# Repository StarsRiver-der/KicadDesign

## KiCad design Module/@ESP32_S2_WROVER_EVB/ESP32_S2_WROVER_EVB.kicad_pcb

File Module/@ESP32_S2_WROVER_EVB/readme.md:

# ESP32-S2-WROVER 评估板 - SmartKnob
* 核心：ESP32-S2-WROVER 4N8R (4MB ROM,8M RAM)
* 串口：CP2102
* 电源：3.3V(MP2145),9V或可调(MP3431)
* 传感：光传感器VEML7700、温度传感器TMP117、6轴加速度传感器BMI160、磁编码器MT6701
* 外设：240x240 LCD串口屏幕(GC9401)、电容触摸屏(CST816)、SD卡、SK6812可编程LED、6PWM驱动器(TMC3600)、ADC(ADS122C04)
* 电机：BLDC-GM4018H

# 功能
* 智能旋钮，参考链接：https://www.youtube.com/watch?v=ip641WmY4pA

# 说明
### 工作模式介绍
* 旋转Knob，改变参数 (通过磁编码器检测)
* 按压Knob，模式切换 (通过SW1微动开关检测)
* Knob根据远程指令\传感器参数自动旋转 (通过控制电机转动)
### 器件功能
* VEML7700 提供环境光强度检测
* TMP117 提供室内温度检测
* BMI160 提供本设备姿态检测
* MT6701 检测电机精确旋转角度
* TMC3600 驱动BLDC电机，提供旋转反馈
* ADS122C04 24位低速高精度ADC，外接模拟信号传感器，如气体传感器、应变片
### 器件控制方式
* VEML7700、TMP117、BMI160、MT6701、ADS122C04、电容屏通过一个I2C总线控制
* LCD串口屏幕、SD卡通过一个SPI串口控制，其中LDC为非标准的四线SPI（CS、SLC、DC、SDA）
* GM4018H通过6线PWM控制

# 预览

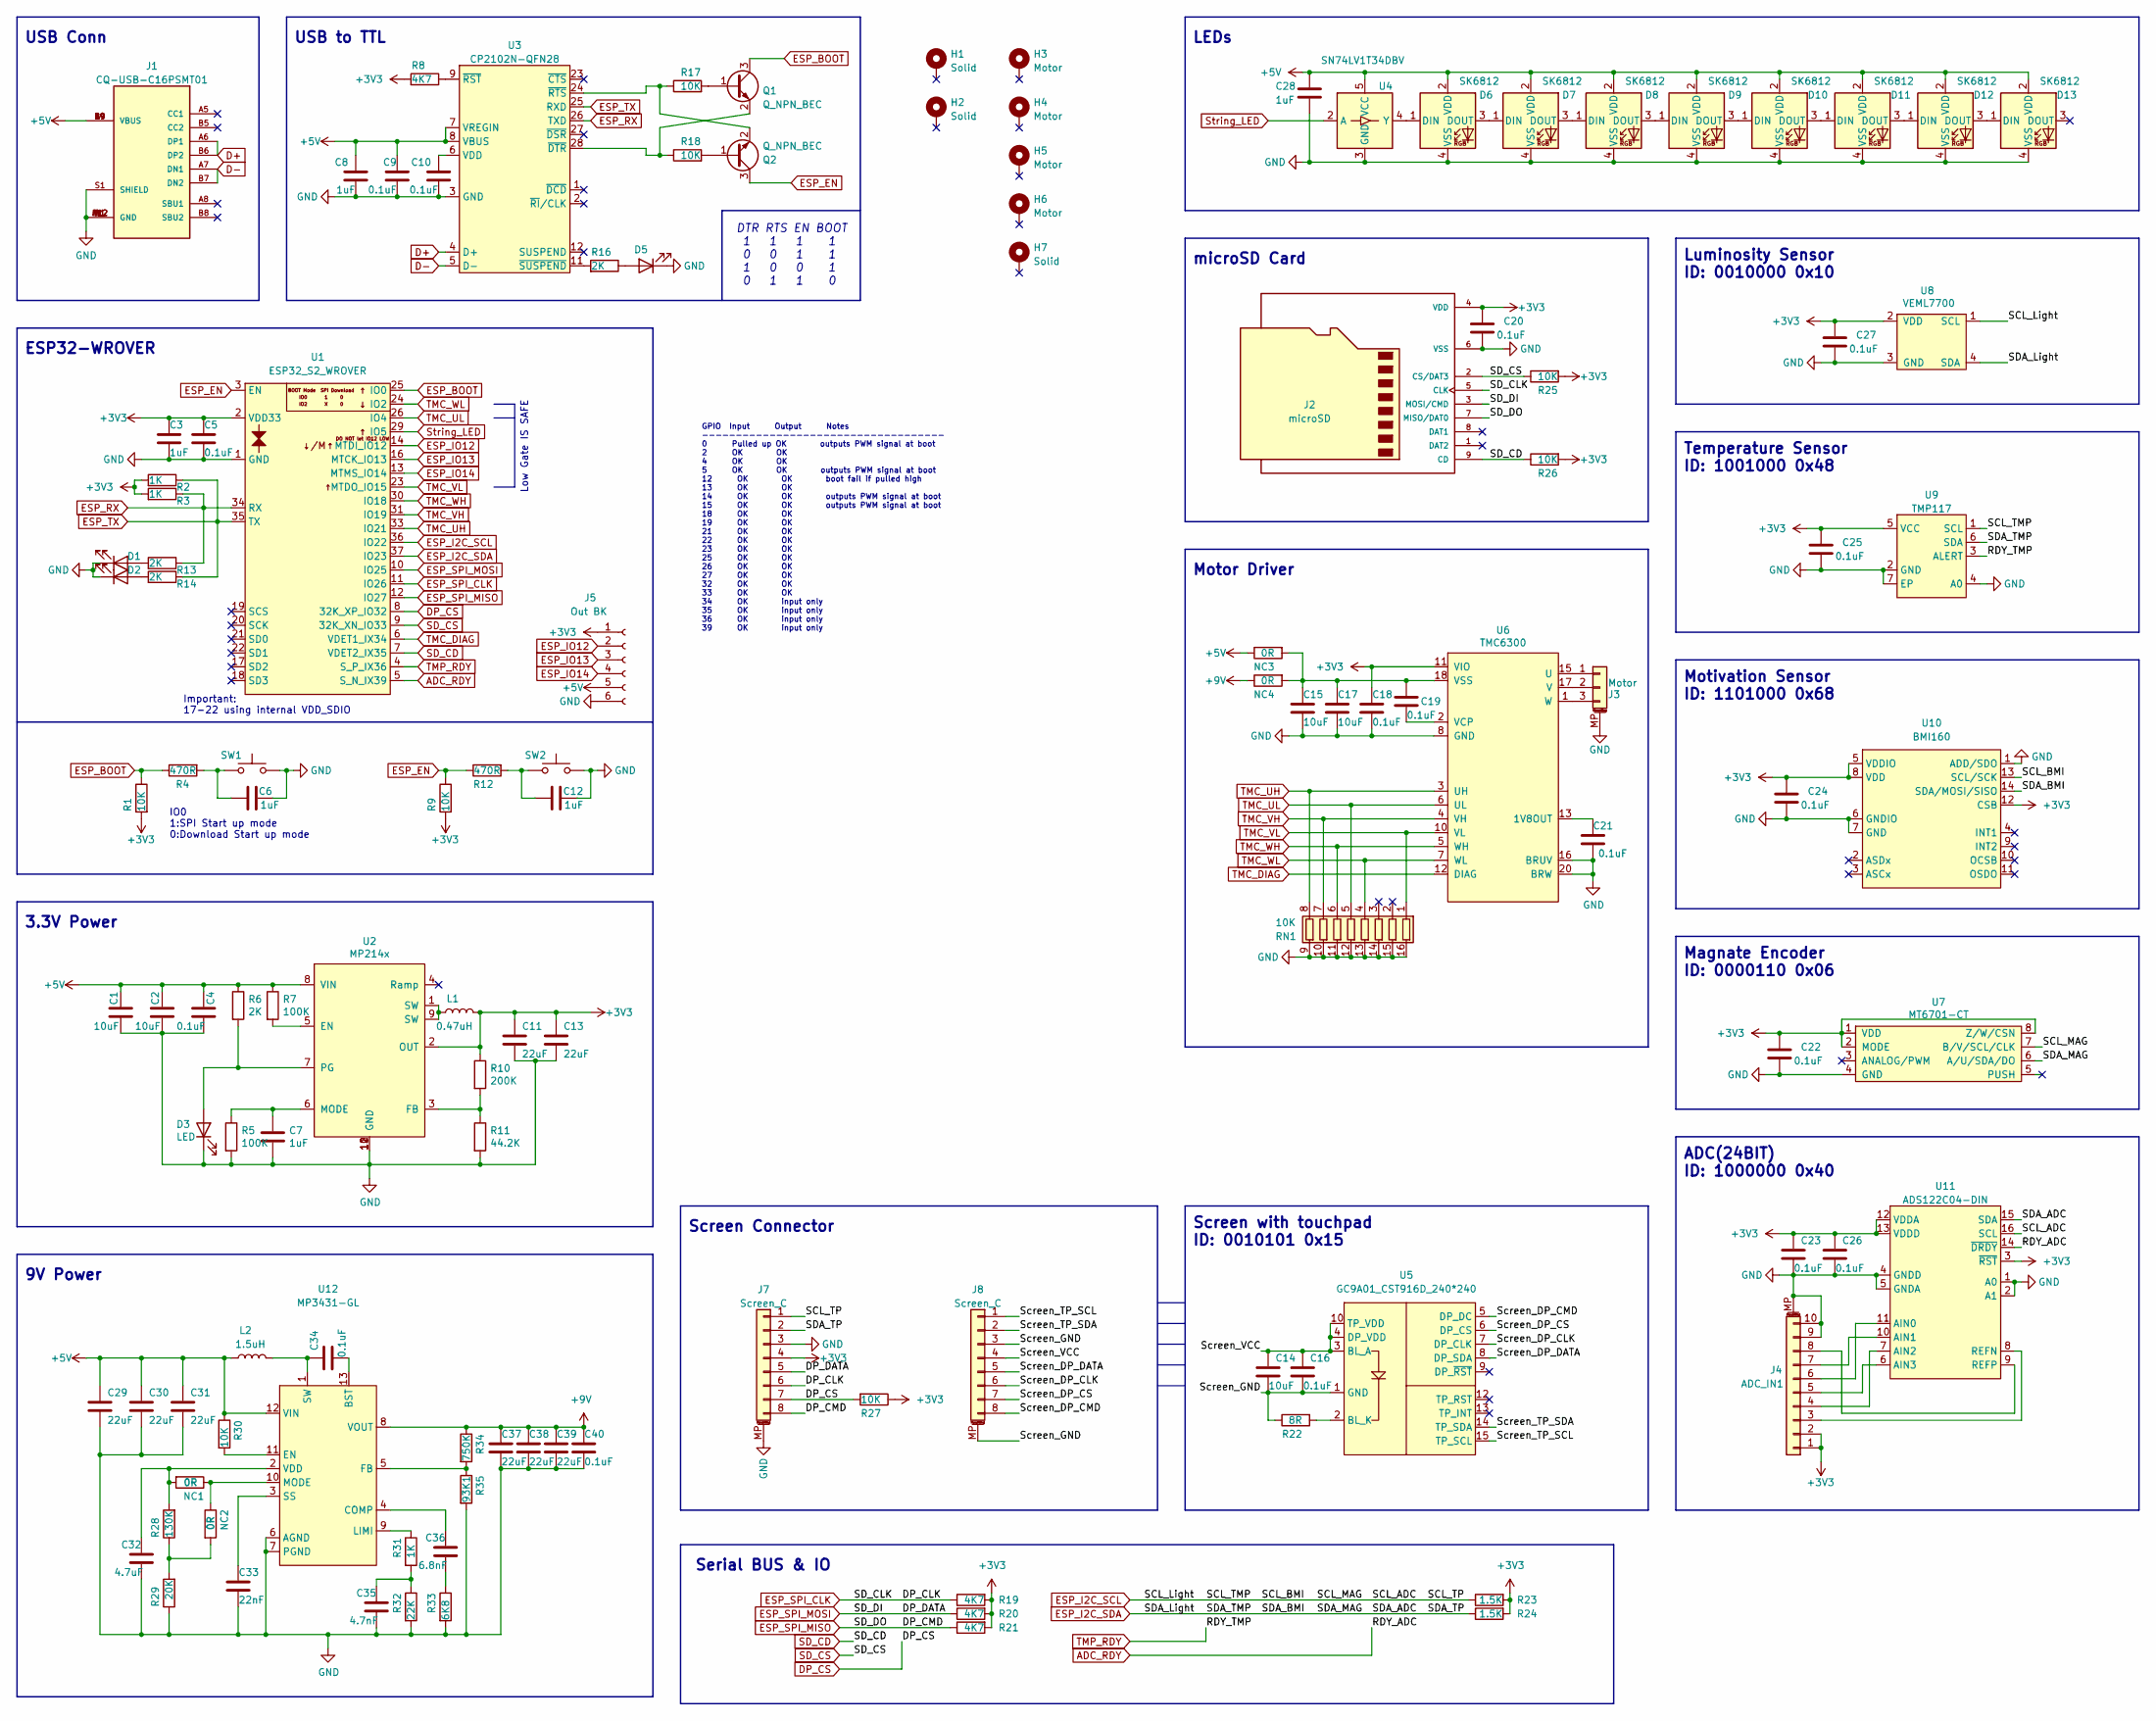
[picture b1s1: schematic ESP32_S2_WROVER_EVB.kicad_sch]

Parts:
C1, C2, C15, C17: 10uF; C_0603_1608Metric
C3, C6, C7, C8, C12, C28: 1uF; C_0402_1005Metric
C4, C5, C9, C10, C16, C18, C19, C20, C21, C22, C23, C24, C25, C26, C27, C34, C40: 0.1uF; C_0402_1005Metric
C11, C13, C29, C30, C31, C37, C38, C39: 22uF; C_0603_1608Metric
C14: 10uF; C_0402_1005Metric
C32: 4.7uF; C_0402_1005Metric
C33: 22nF; C_0402_1005Metric
C35: 4.7nF; C_0402_1005Metric
C36: 6.8nF; C_0402_1005Metric
D1, D2, D3, D5: LED; LED_0402_1005Metric
D6, D7, D8, D9, D10, D11, D12, D13: SK6812; SK6812-4020
H1, H2: Solid; MountingHole_2.2mm_M2_Pad_Via
H3, H4, H5, H6: Motor; MountingHole_3.2mm_M3_Pad_Via
H7: Solid; MountingHole_3.2mm_M3_Pad_Via
J1: CQ-USB-C16PSMT01; USB_C_Receptacle_XKB_U262-16XN-4BVC11; PARTREV A
J2: microSD; PARTREV A
J3: Motor; JST_PH_S3B-PH-SM4-TB_1x03-1MP_P2.00mm_Horizontal; LCSC C293630
J4: ADC_IN1; TE_1-84953-0_1x10-1MP_P1.0mm_Horizontal
J5: Out BK; PinHeader_1x06_P2.54mm_Vertical
J7, J8: Screen_C; TE_84953-8_1x08-1MP_P1.0mm_Horizontal
L1: 0.47uH; L_Taiyo-Yuden_NR-40xx
L2: 1.5uH; L_Wuerth_HCI-5040
NC1, NC2: 0R; R_0402_1005Metric
NC3, NC4: 0R; R_0805_2012Metric
Q1, Q2: Q_NPN_BEC; SOT-23
R1, R9, R17, R18, R25, R26, R27, R30: 10K; R_0402_1005Metric
R2, R3, R31: 1K; R_0402_1005Metric
R4, R12: 470R; R_0402_1005Metric
R5, R7: 100K; R_0402_1005Metric
R6, R13, R14, R16: 2K; R_0402_1005Metric
R8, R19, R20, R21: 4K7; R_0402_1005Metric
R10: 200K; R_0402_1005Metric
R11: 44.2K; R_0402_1005Metric
R22: 8R; R_0603_1608Metric
R23, R24: 1.5K; R_0402_1005Metric
R28: 130K; R_0402_1005Metric
R29: 20K; R_0402_1005Metric
R32: 22K; R_0402_1005Metric
R33: 6K8; R_0402_1005Metric
R34: 750K; R_0402_1005Metric
R35: 93K1; R_0402_1005Metric
RN1: 10K; R_Array_Convex_8x0602
SW1: SW_Push; SW_SPST_EVQP0
SW2: SW_Push; SW_Push_1P1T_NO_Vertical_Wuerth_434133025816
U1: ESP32_S2_WROVER; ESP32-S2-WROVER
U2: MP214x; MP2145
U3: CP2102N-QFN28; QFN-28-1EP_5x5mm_P0.5mm_EP3.35x3.35mm
U4: SN74LV1T34DBV; SOT-23-5
U5: GC9A01_CST916D_240*240; TE_1-1734839-5_1x15-1MP_P0.5mm_Horizontal
U6: TMC6300; QFN-20-1EP_3x3mm_P0.4mm_EP1.65x1.65mm; Digikey TMC6300-LA-T
U7: MT6701-CT; SOIC-8_3.9x4.9mm_P1.27mm; LCSC C2856764
U8: VEML7700; Digikey VEML7700-TT
U9: TMP117; WSON-6-1EP_2x2mm_P0.65mm_EP1x1.6mm
U10: BMI160; Bosch_LGA-14_3x2.5mm_P0.5mm
U11: ADS122C04-DIN; TSSOP-16_4.4x5mm_P0.65mm
U12: MP3431-GL; MP3431

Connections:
+3V3: C3.1, C5.1, C11.1, C13.1, C18.1, C20.1, C22.1, C23.1, C24.1, C25.1, C26.1, C27.1, J2.4 (VDD), J4.1, J4.2, J5.1, J7.4, L1.2, R1.2, R2.2, R3.2, R8.2, R9.2, R10.1, R19.2, R20.2, R21.2, R23.2, R24.2, R25.2, R26.2, R27.1, U1.2 (VDD33), U2.2 (OUT), U6.11 (VIO), U7.1 (VDD), U7.2 (MODE), U7.8 (Z/W/CSN), U8.2 (VDD), U9.5 (VCC), U10.5 (VDDIO), U10.8 (VDD), U10.12 (CSB), U11.3 (~RST), U11.12 (VDDA), U11.13 (VDDD)
+5V: C1.1, C2.1, C4.1, C8.2, C9.2, C28.1, C29.1, C30.1, C31.1, D6.2 (VDD), D7.2 (VDD), D8.2 (VDD), D9.2 (VDD), D10.2 (VDD), D11.2 (VDD), D12.2 (VDD), D13.2 (VDD), J1.A4 (VBUS), J1.A9 (VBUS), J1.B4 (VBUS), J1.B9 (VBUS), J5.5, L2.1, NC3.1, R6.1, R7.1, R30.1, U2.8 (VIN), U3.7 (VREGIN), U3.8 (VBUS), U4.5 (VCC), U12.12 (VIN)
+9V: C37.1, C38.1, C39.1, C40.1, NC4.1, R34.1, U12.8 (VOUT)
/Screen_DP_CLK: J8.6, U5.7 (DP_CLK)
/Screen_DP_CMD: J8.8, U5.5 (DP_DC)
/Screen_DP_CS: J8.7, U5.6 (DP_CS)
/Screen_DP_DATA: J8.5, U5.8 (DP_SDA)
/Screen_GND: C14.2, C16.2, J8.3, J8.MP (MountPin), R22.1, U5.1 (GND), U5.11 (GND), U5.MP
/Screen_TP_SCL: J8.1, U5.15 (TP_SCL)
/Screen_TP_SDA: J8.2, U5.14 (TP_SDA)
/Screen_VCC: C14.1, C16.1, J8.4, U5.3 (BL_A), U5.4 (DP_VDD), U5.10 (TP_VDD)
ADC_RDY: U1.5 (S_N_IX39), U11.14 (~DRDY)
D+: J1.A6 (DP1), J1.B6 (DP2), U3.4 (D+)
D-: J1.A7 (DN1), J1.B7 (DN2), U3.5 (D-)
DP_CS: J7.7, R27.2, U1.8 (32K_XP_IO32)
ESP_BOOT: Q1.3 (C), R1.1, R4.1, U1.25 (IO0)
ESP_EN: Q2.3 (C), R9.1, R12.1, U1.3 (EN)
ESP_I2C_SCL: J7.1, R23.1, U1.36 (IO22), U7.7 (B/V/SCL/CLK), U8.1 (SCL), U9.1 (SCL), U10.13 (SCL/SCK), U11.16 (SCL)
ESP_I2C_SDA: J7.2, R24.1, U1.37 (IO23), U7.6 (A/U/SDA/DO), U8.4 (SDA), U9.6 (SDA), U10.14 (SDA/MOSI/SISO), U11.15 (SDA)
ESP_IO12: J5.2, U1.14 (MTDI_IO12)
ESP_IO13: J5.3, U1.16 (MTCK_IO13)
ESP_IO14: J5.4, U1.13 (MTMS_IO14)
ESP_RX: R3.1, R13.1, U1.34 (RX), U3.26 (TXD)
ESP_SPI_CLK: J2.5 (CLK), J7.6, R19.1, U1.11 (IO26)
ESP_SPI_MISO: J2.7 (MISO/DAT0), J7.8, R21.1, U1.12 (IO27)
ESP_SPI_MOSI: J2.3 (MOSI/CMD), J7.5, R20.1, U1.10 (IO25)
ESP_TX: R2.1, R14.1, U1.35 (TX), U3.25 (RXD)
GND: C1.2, C2.2, C3.2, C4.2, C5.2, C6.2, C7.2, C8.1, C9.1, C10.2, C11.2, C12.2, C13.2, C15.2, C17.2, C18.2, C20.2, C21.1, C22.2, C23.2, C24.2, C25.2, C26.2, C27.2, C28.2, C29.2, C30.2, C31.2, C32.2, C33.2, C35.2, C37.2, C38.2, C39.2, C40.2, D1.1 (K), D2.1 (K), D3.1 (K), D5.1 (K), D6.4 (VSS), D7.4 (VSS), D8.4 (VSS), D9.4 (VSS), D10.4 (VSS), D11.4 (VSS), D12.4 (VSS), D13.4 (VSS), J1.A1 (GND), J1.A12 (GND), J1.B1 (GND), J1.B12 (GND), J1.S1 (SHIELD), J2.6 (VSS), J2.10 (SHIELD), J3.MP (MountPin), J4.9, J4.10, J4.MP (MountPin), J5.6, J7.3, J7.MP (MountPin), R5.2, R11.2, R29.1, R32.2, R33.2, R35.2, RN1.9 (R8.2), RN1.10 (R7.2), RN1.11 (R6.2), RN1.12 (R5.2), RN1.13 (R4.2), RN1.14 (R3.2), RN1.15 (R2.2), RN1.16 (R1.2), SW1.2, SW2.2, U1.1 (GND), U1.15 (GND), U1.38 (GND), U1.39 (GND), U2.10 (GND), U2.11 (GND), U2.12 (GND), U3.3 (GND), U3.29 (GND), U4.3 (GND), U6.8 (GND), U6.9 (GND), U6.14 (GND), U6.16 (BRUV), U6.20 (BRW), U6.21 (EP), U7.4 (GND), U8.3 (GND), U9.2 (GND), U9.4 (A0), U9.7 (EP), U10.1 (ADD/SDO), U10.6 (GNDIO), U10.7 (GND), U11.1 (A0), U11.2 (A1), U11.4 (GNDD), U11.5 (GNDA), U12.6 (AGND), U12.7 (PGND)
unnamed: C6.1, R4.2, SW1.1
unnamed: C7.1, R5.1, U2.6 (MODE)
unnamed: C10.1, U3.6 (VDD)
unnamed: C12.1, R12.2, SW2.1
unnamed: C15.1, C17.1, C19.1, NC3.2, NC4.2, U6.18 (VSS)
unnamed: C19.2, U6.2 (VCP)
unnamed: C21.2, U6.13 (1V8OUT)
unnamed: C32.1, NC1.2, R28.2, U12.2 (VDD)
unnamed: C33.1, U12.3 (SS)
unnamed: C34.1, L2.2, U12.1 (SW)
unnamed: C34.2, U12.13 (BST)
unnamed: C35.1, R31.2, R32.1
unnamed: C36.1, U12.4 (COMP)
unnamed: C36.2, R33.1
unnamed: D1.2 (A), R13.2
unnamed: D2.2 (A), R14.2
unnamed: D3.2 (A), R6.2, U2.7 (PG)
unnamed: D5.2 (A), R16.1
unnamed: D6.1 (DIN), U4.4 (Y)
unnamed: D6.3 (DOUT), D7.1 (DIN)
unnamed: D7.3 (DOUT), D8.1 (DIN)
unnamed: D8.3 (DOUT), D9.1 (DIN)
unnamed: D9.3 (DOUT), D10.1 (DIN)
unnamed: D10.3 (DOUT), D11.1 (DIN)
unnamed: D11.3 (DOUT), D12.1 (DIN)
unnamed: D12.3 (DOUT), D13.1 (DIN)
unnamed: J3.1, U6.15 (U)
unnamed: J3.2, U6.17 (V)
unnamed: J3.3, U6.1 (W)
unnamed: J4.3, U11.8 (REFN)
unnamed: J4.4, U11.7 (AIN2)
unnamed: J4.5, U11.6 (AIN3)
unnamed: J4.6, U11.11 (AIN0)
unnamed: J4.7, U11.10 (AIN1)
unnamed: J4.8, U11.9 (REFP)
unnamed: L1.1, U2.1 (SW), U2.9 (SW)
unnamed: NC1.1, NC2.1, U12.10 (MODE)
unnamed: NC2.2, R28.1, R29.2
unnamed: Q1.1 (B), R17.2
unnamed: Q1.2 (E), R18.1, U3.28 (~DTR)
unnamed: Q2.1 (B), R18.2
unnamed: Q2.2 (E), R17.1, U3.24 (~RTS)
unnamed: R7.2, U2.5 (EN)
unnamed: R8.1, U3.9 (~RST)
unnamed: R10.2, R11.1, U2.3 (FB)
unnamed: R16.2, U3.11 (~SUSPEND)
unnamed: R22.2, U5.2 (BL_K)
unnamed: R30.2, U12.11 (EN)
unnamed: R31.1, U12.9 (LIMI)
unnamed: R34.2, R35.1, U12.5 (FB)
SD_CD: J2.9 (CD), R26.1, U1.7 (VDET2_IX35)
SD_CS: J2.2 (CS/DAT3), R25.1, U1.9 (32K_XN_IO33)
String_LED: U1.29 (IO5), U4.2 (A)
TMC_DIAG: U1.6 (VDET1_IX34), U6.12 (DIAG)
TMC_UH: RN1.8 (R8.1), U1.33 (IO21), U6.3 (UH)
TMC_UL: RN1.5 (R5.1), U1.26 (IO4), U6.6 (UL)
TMC_VH: RN1.7 (R7.1), U1.31 (IO19), U6.4 (VH)
TMC_VL: RN1.1 (R1.1), U1.23 (MTDO_IO15), U6.10 (VL)
TMC_WH: RN1.6 (R6.1), U1.30 (IO18), U6.5 (WH)
TMC_WL: RN1.4 (R4.1), U1.24 (IO2), U6.7 (WL)
TMP_RDY: U1.4 (S_P_IX36), U9.3 (ALERT)

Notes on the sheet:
Magnate Encoder ID: 0000110 0x06
Screen with touchpad ID: 0010101 0x15
microSD Card
GPIO Input Output Notes ------------------------------------ 0 Pulled up OK outputs PWM signal at boot 2 OK OK 4 OK OK 5 OK OK outputs PWM signal at boot 12 OK OK boot fail if pulled high 13 OK OK 14 OK OK outputs PWM signal at boot 15 OK OK outputs PWM signal at boot 18 OK OK 19 OK OK 21 OK OK 22 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
Motor Driver
3.3V Power
ESP32-WROVER
Serial BUS & IO
Temperature Sensor ID: 1001000 0x48
USB to TTL
9V Power
Luminosity Sensor ID: 0010000 0x10
Motivation Sensor ID: 1101000 0x68
IO0 1:SPI Start up mode 0:Download Start up mode
USB Conn
DTR RTS EN BOOT 1 1 1 1 0 0 1 1 1 0 0 1 0 1 1 0
LEDs
Important: 17-22 using internal VDD_SDIO
Screen Connector
ADC(24BIT) ID: 1000000 0x40
Low Gate IS SAFE

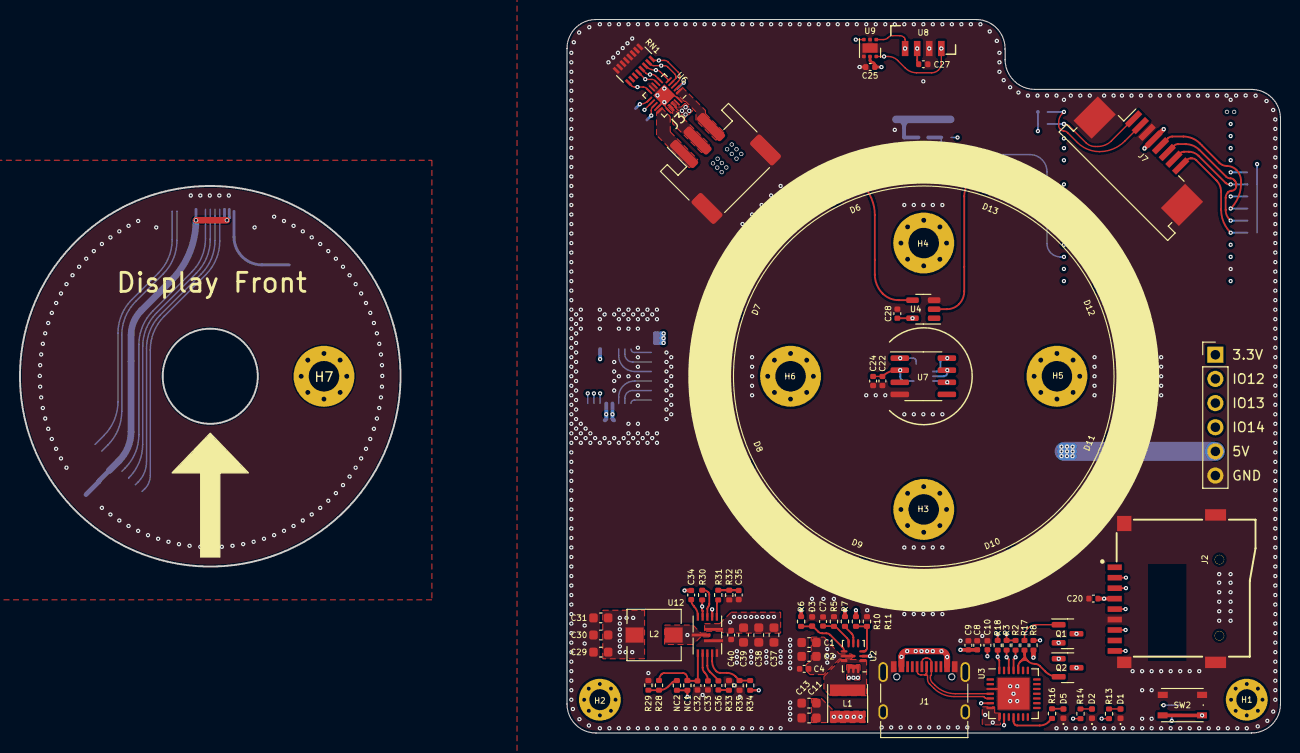
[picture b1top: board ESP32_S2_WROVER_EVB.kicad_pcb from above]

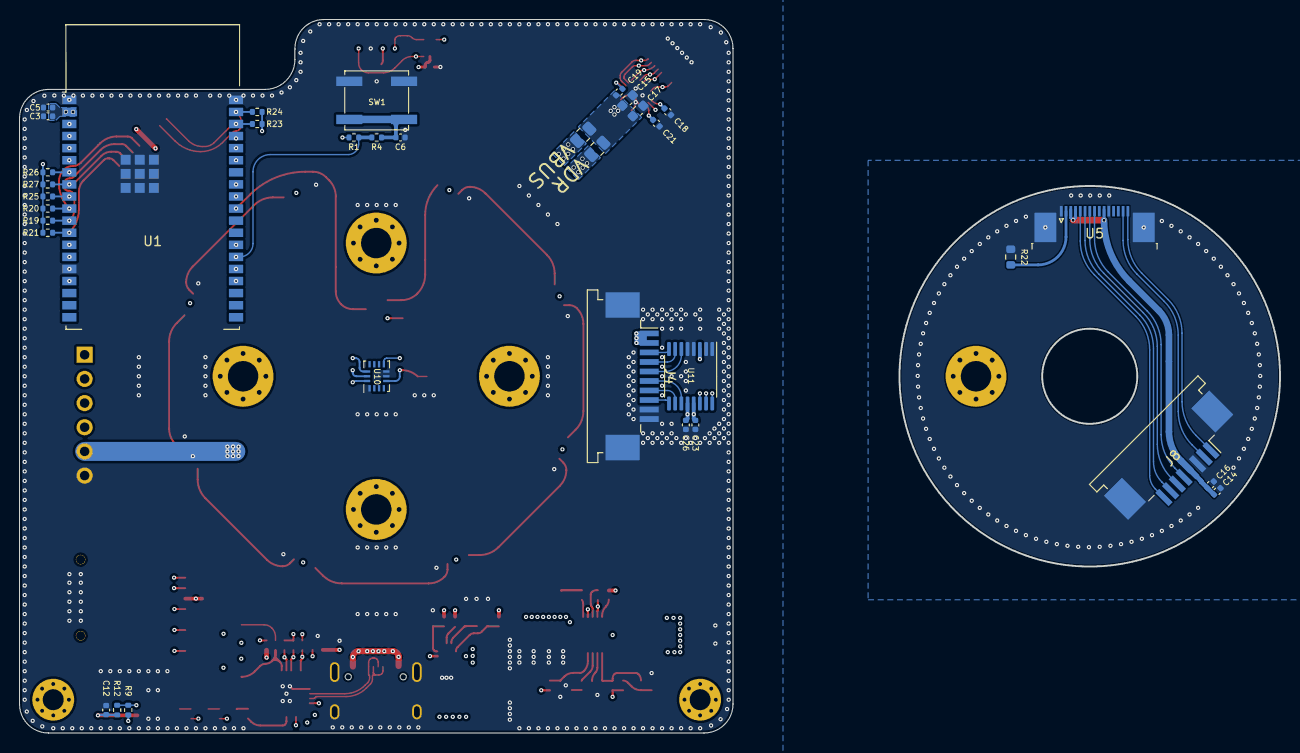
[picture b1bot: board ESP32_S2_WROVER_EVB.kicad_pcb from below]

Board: 4 copper layers, 75.0 x 75.0 mm, 123 parts (35 on the bottom side), 89 nets.

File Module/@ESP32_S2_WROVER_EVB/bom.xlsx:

元件 | 数量/板 | 值 | 封装 | 备注 | 数量 | 单价 | 总价
R00 | 2 | 0R | 0402 |  | 0 | 0
R000 | 2 | 0R | 0805 |  | 0 | 0
R1, R9, R17, R18, R25, R26, R27, R30 | 8 | 10K | 0402 |  | 0 | 0
R2, R3, R6, R16 | 4 | 2K | 0402 |  | 0 | 0
R4, R12 | 2 | 470R | 0402 |  | 0 | 0
R5, R7 | 2 | 100K | 0402 |  | 0 | 0
R8, R19, R20, R21 | 4 | 4K7 | 0402 |  | 0 | 0
R10 | 1 | 200K | 0402 |  | 0 | 0
R11 | 1 | 44.2K | 0402 |  | 0 | 0
R22 | 1 | 8R | 0603 |  | 0 | 0
R23, R24 | 2 | 1.5K | 0402 |  | 0 | 0
R28 | 1 | 130K | 0402 |  | 0 | 0
R29 | 1 | 20K | 0402 |  | 0 | 0
R31 | 1 | 1K | 0402 |  | 0 | 0
R32 | 1 | 22K | 0402 |  | 0 | 0
R33 | 1 | 6K8 | 0402 |  | 0 | 0
R34 | 1 | 750K | 0402 |  | 0 | 0
R35 | 1 | 93K1 | 0402 |  | 0 | 0
RN1 | 1 | 10K | 8x0602 | 排阻8x0602 | 0 | 0
L1 | 1 | 0.47uH | NR4020 | 磁胶电感 | 0 | 0
L2 | 1 | 1.5uH | 5040 |  | 0 | 0
C1, C2, C15, C17 | 4 | 10uF | 0603 |  | 0 | 0
C3, C6, C7, C8, C12, C28 | 6 | 1uF | 0402 |  | 0 | 0
C4, C5, C9, C10, C16, C18, C19, C20, C21, C22, C23, C24, C25, C26, C27, C34, C40 | 17 | 0.1uF | 0402 |  | 0 | 0
C11, C13, C29, C30, C31, C37, C38, C39 | 8 | 22uF | 0603 |  | 0 | 0
C14 | 1 | 10uF | 0402 |  | 0 | 0
C32 | 1 | 4.7uF | 0402 |  | 0 | 0
C33 | 1 | 22nF | 0402 |  | 0 | 0
C35 | 1 | 4.7nF | 0402 |  | 0 | 0
C36 | 1 | 6.8nF | 0402 |  | 0 | 0
D1, D2, D3, D5 | 4 | LED | 0402 |  | 0 | 0
D6, D7, D8, D9, D10, D11, D12, D13 | 8 | SK6812-4020 | SK6812-4020 | 侧发光，不能用WS2812 | 0 | 0
J1 | 1 | Type-C 16pin | Type-C 16pin | https://detail.tmall.com/item.htm?id=617881556896&spm=a1z09.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 | 0 | 0
J2 | 1 | microSD | microSD槽 | https://detail.tmall.com/item.htm?id=615194188570&spm=a1z09.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 | 0 | 0
J3 | 1 | Motor | PH2.00 3P卧贴 | https://item.taobao.com/item.htm?spm=a1z2k.11010449.931864.2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 | 0 | 0
J4 | 1 | ADC_IN1 | 抽拉上接 10p-1mm | https://item.taobao.com/item.htm?spm=a230r.1.14.29.5d1b6f3bt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 | 0 | 0
J7, J8 | 2 | Screen_C | 抽拉上接 8p-1mm | https://item.taobao.com/item.htm?spm=a230r.1.14.29.5d1b6f3bt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 | 0 | 0
U5 | 1 | Screen_Conn | 抽拉上接 15p-0.5mm | https://item.taobao.com/item.htm?spm=a230r.1.14.29.5d1b6f3bt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 | 0 | 0
Q1, Q2 | 2 | S8050 - NPN | SOT-23 |  | 0 | 0
SW1 | 1 | SW_Push | 3.5mm | https://item.taobao.com/item.htm?spm=a230r.1.14.188.1c6d7fd0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 | 0 | 0
SW2 | 1 | SW_Push | 3*4*2.5 包脚 | https://detail.tmall.com/item.htm?id=654795333730&spm=a1z09.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 | 0 | 0
U1 | 1 | ESP32_S2_WROVER | ESP32-S2-WROVER |  | 0 | 0
U2 | 1 | MP2145 | MP2145 |  | 0 | 0
U3 | 1 | CP2102 | QFN28 |  | 0 | 0
U4 | 1 | SN74LV1T34DBV | SOT-23-5 |  | 0 | 0
U6 | 1 | TMC6300_LA | QFN-20 |  | 0 | 0
U7 | 1 | MT6701 | SOIC-8 |  | 0 | 0
U8 | 1 | VEML7700 | VEML7700 |  | 0 | 0
U9 | 1 | TMP117 | WSON-6 |  | 0 | 0
U10 | 1 | BMI160 | LGA-14 |  | 0 | 0
U11 | 1 | ADS122C04-DIN | TSSOP-16 |  | 0 | 0
U12 | 1 | MP3431-GL | MP3431 |  | 0 | 0
M1 | 1 | 电机 | GM4018H | https://item.taobao.com/item.htm?spm=a1z0d.6639537/tb.199719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 | 0 | 0

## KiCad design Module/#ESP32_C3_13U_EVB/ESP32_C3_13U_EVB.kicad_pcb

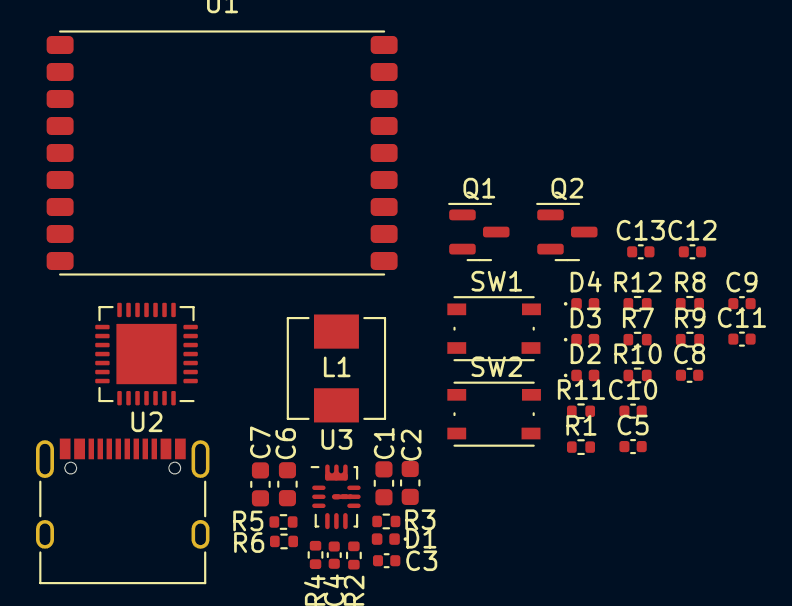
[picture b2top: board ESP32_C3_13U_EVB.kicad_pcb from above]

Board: 2 copper layers, 38 parts (0 on the bottom side), 22 nets, no tracks yet.

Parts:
C1, C2: 10uF; C_0603_1608Metric
C3, C8, C9, C11: 0.1uF; C_0402_1005Metric
C4, C5, C10, C12, C13: 1uF; C_0402_1005Metric
C6, C7: 22uF; C_0603_1608Metric
D1, D2, D3, D4: LED; LED_0402_1005Metric
J1: CQ-USB-C16PSMT01; USB_C_Receptacle_XKB_U262-16XN-4BVC11
L1: 0.47uH; L_Sunlord_MWSA0518_5.4x5.2mm
Q1, Q2: Q_NPN_BEC; SOT-23
R1: 4K7; R_0402_1005Metric
R2, R4: 100K; R_0402_1005Metric
R3, R7, R8, R9: 2K; R_0402_1005Metric
R5: 200K; R_0402_1005Metric
R6: 44.2K; R_0402_1005Metric
R10, R11, R12: 10K; R_0402_1005Metric
SW1, SW2: SW_Push; SW_Push_1P1T_NO_Vertical_Wuerth_434133025816
U1: C3_13U; ESP32_C3_13U
U2: CP2102N-QFN28; QFN-28-1EP_5x5mm_P0.5mm_EP3.35x3.35mm
U3: MP214x; MP2145

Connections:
3.3V: C6.1, C7.1, C10.1, C11.1, L1.2, R1.2, R5.1, R8.2, R9.2, R12.2, U1.1 (VCC), U3.2 (OUT)
5V: C1.1, C2.1, C3.1, C5.2, C8.2, J1.A4 (VBUS), J1.A9 (VBUS), J1.B4 (VBUS), J1.B9 (VBUS), R3.1, R4.1, U2.7 (VREGIN), U2.8 (VBUS), U3.8 (VIN)
D+: J1.A6 (DP1), J1.B6 (DP2), U2.4 (D+)
D-: J1.A7 (DN1), J1.B7 (DN2), U2.5 (D-)
ESP_BOOT: C13.2, Q1.3 (C), R12.1, SW2.1, U1.8 (IO9)
ESP_EN: C12.2, Q2.3 (C), SW1.1, U1.2 (EN)
ESP_RX: D4.2 (A), R9.1, U1.11 (RX), U2.26 (TXD)
ESP_TX: D3.2 (A), R8.1, U1.12 (TX), U2.25 (RXD)
GND: C1.2, C2.2, C3.2, C4.2, C5.1, C6.2, C7.2, C8.1, C9.2, C10.2, C11.2, C12.1, C13.1, D1.1 (K), D2.1 (K), D3.1 (K), D4.1 (K), J1.A1 (GND), J1.A12 (GND), J1.B1 (GND), J1.B12 (GND), J1.S1 (SHIELD), R2.2, R6.2, SW1.2, SW2.2, U1.9 (GND), U2.3 (GND), U2.29 (GND), U3.10 (GND), U3.11 (GND), U3.12 (GND)
unnamed: C4.1, R2.1, U3.6 (MODE)
unnamed: C9.1, U2.6 (VDD)
unnamed: D1.2 (A), R3.2, U3.7 (PG)
unnamed: D2.2 (A), R7.1
unnamed: L1.1, U3.1 (SW), U3.9 (SW)
unnamed: Q1.1 (B), R10.2
unnamed: Q1.2 (E), R11.1, U2.28 (~DTR)
unnamed: Q2.1 (B), R11.2
unnamed: Q2.2 (E), R10.1, U2.24 (~RTS)
unnamed: R1.1, U2.9 (~RST)
unnamed: R4.2, U3.5 (EN)
unnamed: R5.2, R6.1, U3.3 (FB)
unnamed: R7.2, U2.11 (~SUSPEND)

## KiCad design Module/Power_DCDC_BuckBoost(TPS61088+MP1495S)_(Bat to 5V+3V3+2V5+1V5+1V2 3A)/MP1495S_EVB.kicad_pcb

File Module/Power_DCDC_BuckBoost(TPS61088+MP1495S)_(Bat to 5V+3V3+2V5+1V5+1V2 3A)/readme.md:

# 2.8V-4.2V 锂电池输入的 DCDC 单极性多轨电源
* 工作温度：0-85℃
* 5V、3v3、2v5、1v5、1v2多轨输出
* 最高20W输出

# 注意事项
* 使用Kicad6绘制

# 原理
见说明手册

# 接口
* 电压输入和控制输入：FPC_Hirose_FH12-14S
* 电压输出和控制输出：PCI_1x

# 预览

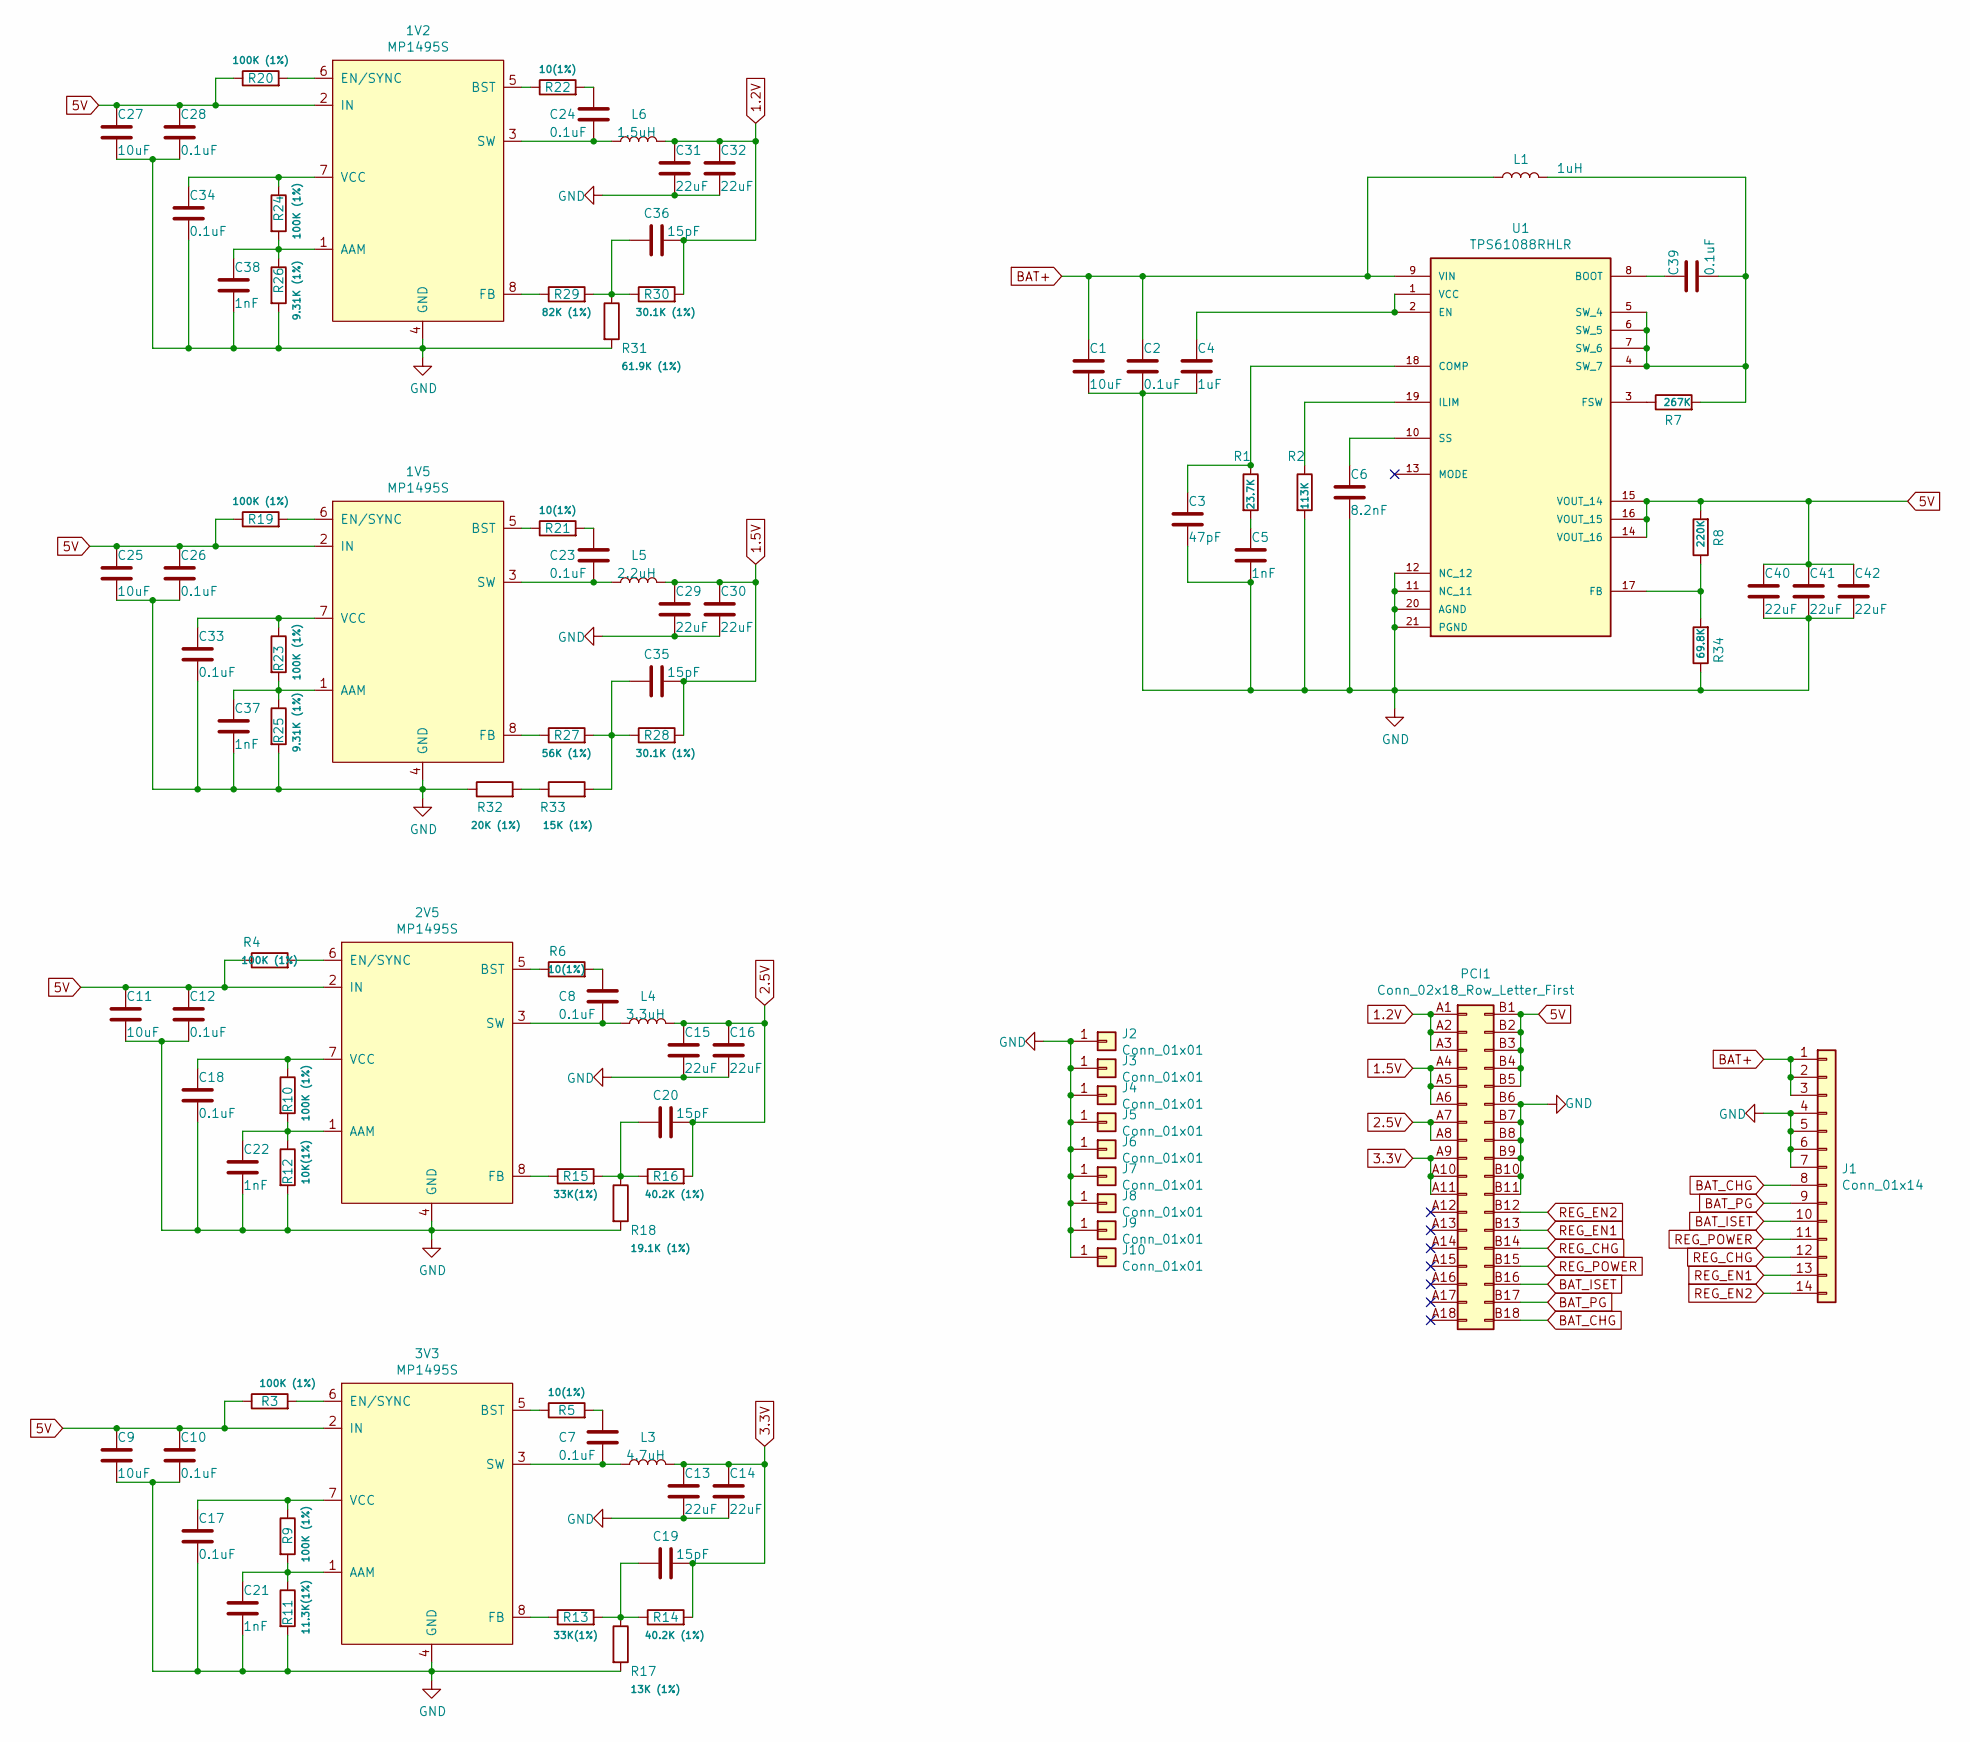
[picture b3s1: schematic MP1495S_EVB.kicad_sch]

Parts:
1V2, 1V5, 2V5, 3V3: MP1495S; SOT65P280X100-8N
C1, C9, C11, C25, C27: 10uF; C_0603_1608Metric
C2, C7, C8, C10, C12, C17, C18, C23, C24, C26, C28, C33, C34, C39: 0.1uF; C_0402_1005Metric
C3: 47pF; C_0402_1005Metric
C4: 1uF; C_0402_1005Metric
C5, C21, C22, C37, C38: 1nF; C_0402_1005Metric
C6: 8.2nF; C_0402_1005Metric
C13, C14, C15, C16, C29, C30, C31, C32, C40, C41, C42: 22uF; C_0603_1608Metric
C19, C20, C35, C36: 15pF; C_0402_1005Metric
J1: Conn_01x14; Hirose_FH12-14S-0.5SH_1x14-1MP_P0.50mm_Horizontal
J2, J3, J4, J5, J6, J7, J8, J9, J10: Conn_01x01; pad-6-1.5
L1: 1uH; L_Sunlord_MWSA0518_5.4x5.2mm
L3: 4.7uH; L_Sunlord_MWSA0518_5.4x5.2mm
L4: 3.3uH; L_Sunlord_MWSA0518_5.4x5.2mm
L5: 2.2uH; L_Sunlord_MWSA0518_5.4x5.2mm
L6: 1.5uH; L_Sunlord_MWSA0518_5.4x5.2mm
PCI1: Conn_02x18_Row_Letter_First; BUS_PCIexpress_x1
R1: 23.7K; R_0402_1005Metric
R2: 113K; R_0402_1005Metric
R3, R4, R9, R10, R19, R20, R23, R24: 100K (1%); R_0402_1005Metric
R5, R6, R21, R22: 10(1%); R_0402_1005Metric
R7: 267K; R_0402_1005Metric
R8: 220K; R_0402_1005Metric
R11: 11.3K(1%); R_0402_1005Metric
R12: 10K(1%); R_0402_1005Metric
R13, R15: 33K(1%); R_0402_1005Metric
R14, R16: 40.2K (1%); R_0402_1005Metric
R17: 13K (1%); R_0402_1005Metric
R18: 19.1K (1%); R_0402_1005Metric
R25, R26: 9.31K (1%); R_0402_1005Metric
R27: 56K (1%); R_0402_1005Metric
R28, R30: 30.1K (1%); R_0402_1005Metric
R29: 82K (1%); R_0402_1005Metric
R31: 61.9K (1%); R_0402_1005Metric
R32: 20K (1%); R_0402_1005Metric
R33: 15K (1%); R_0402_1005Metric
R34: 69.8K; R_0402_1005Metric
U1: TPS61088RHLR; IC_TPS61088RHLR; PARTREV 4219071/A 05/2017

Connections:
1.2V: C31.1, C32.1, C36.2, L6.2, PCI1.A1, PCI1.A2, PCI1.A3, R30.2
1.5V: C29.1, C30.1, C35.2, L5.2, PCI1.A4, PCI1.A5, PCI1.A6, R28.2
2.5V: C15.1, C16.1, C20.2, L4.2, PCI1.A7, PCI1.A8, R16.2
3.3V: C13.1, C14.1, C19.2, L3.2, PCI1.A9, PCI1.A10, PCI1.A11, R14.2
5V: 1V2.2 (IN), 1V5.2 (IN), 2V5.2 (IN), 3V3.2 (IN), C9.1, C10.1, C11.1, C12.1, C25.1, C26.1, C27.1, C28.1, C40.1, C41.1, C42.1, PCI1.B1, PCI1.B2, PCI1.B3, PCI1.B4, PCI1.B5, R3.1, R4.1, R8.2, R19.1, R20.1, U1.14 (VOUT_16), U1.15 (VOUT_14), U1.16 (VOUT_15)
BAT+: C1.1, C2.1, J1.1, J1.2, J1.3, L1.1, U1.9 (VIN)
BAT_CHG: J1.8, PCI1.B18
BAT_ISET: J1.10, PCI1.B16
BAT_PG: J1.9, PCI1.B17
GND: 1V2.4 (GND), 1V5.4 (GND), 2V5.4 (GND), 3V3.4 (GND), C1.2, C2.2, C3.2, C4.2, C5.2, C6.2, C9.2, C10.2, C11.2, C12.2, C13.2, C14.2, C15.2, C16.2, C17.2, C18.2, C21.2, C22.2, C25.2, C26.2, C27.2, C28.2, C29.2, C30.2, C31.2, C32.2, C33.2, C34.2, C37.2, C38.2, C40.2, C41.2, C42.2, J1.4, J1.5, J1.6, J1.7, J2.1, J3.1, J4.1, J5.1, J6.1, J7.1, J8.1, J9.1, J10.1, PCI1.B6, PCI1.B7, PCI1.B8, PCI1.B9, PCI1.B10, PCI1.B11, R2.2, R11.2, R12.2, R17.2, R18.2, R25.2, R26.2, R31.2, R32.1, R34.1, U1.11 (NC_11), U1.12 (NC_12), U1.20 (AGND), U1.21 (PGND)
unnamed: 1V2.1 (AAM), C38.1, R24.2, R26.1
unnamed: 1V2.3 (SW), C24.2, L6.1
unnamed: 1V2.5 (BST), R22.1
unnamed: 1V2.6 (EN/SYNC), R20.2
unnamed: 1V2.7 (VCC), C34.1, R24.1
unnamed: 1V2.8 (FB), R29.1
unnamed: 1V5.1 (AAM), C37.1, R23.2, R25.1
unnamed: 1V5.3 (SW), C23.2, L5.1
unnamed: 1V5.5 (BST), R21.1
unnamed: 1V5.6 (EN/SYNC), R19.2
unnamed: 1V5.7 (VCC), C33.1, R23.1
unnamed: 1V5.8 (FB), R27.1
unnamed: 2V5.1 (AAM), C22.1, R10.2, R12.1
unnamed: 2V5.3 (SW), C8.2, L4.1
unnamed: 2V5.5 (BST), R6.1
unnamed: 2V5.6 (EN/SYNC), R4.2
unnamed: 2V5.7 (VCC), C18.1, R10.1
unnamed: 2V5.8 (FB), R15.1
unnamed: 3V3.1 (AAM), C21.1, R9.2, R11.1
unnamed: 3V3.3 (SW), C7.2, L3.1
unnamed: 3V3.5 (BST), R5.1
unnamed: 3V3.6 (EN/SYNC), R3.2
unnamed: 3V3.7 (VCC), C17.1, R9.1
unnamed: 3V3.8 (FB), R13.1
unnamed: C3.1, R1.1, U1.18 (COMP)
unnamed: C4.1, U1.1 (VCC), U1.2 (EN)
unnamed: C5.1, R1.2
unnamed: C6.1, U1.10 (SS)
unnamed: C7.1, R5.2
unnamed: C8.1, R6.2
unnamed: C19.1, R13.2, R14.1, R17.1
unnamed: C20.1, R15.2, R16.1, R18.1
unnamed: C23.1, R21.2
unnamed: C24.1, R22.2
unnamed: C35.1, R27.2, R28.1, R33.2
unnamed: C36.1, R29.2, R30.1, R31.1
unnamed: C39.1, U1.8 (BOOT)
unnamed: C39.2, L1.2, R7.2, U1.4 (SW_7), U1.5 (SW_4), U1.6 (SW_5), U1.7 (SW_6)
unnamed: R2.1, U1.19 (ILIM)
unnamed: R7.1, U1.3 (FSW)
unnamed: R32.2, R33.1
unnamed: R8.1, R34.2, U1.17 (FB)
REG_CHG: J1.12, PCI1.B14
REG_EN1: J1.13, PCI1.B13
REG_EN2: J1.14, PCI1.B12
REG_POWER: J1.11, PCI1.B15

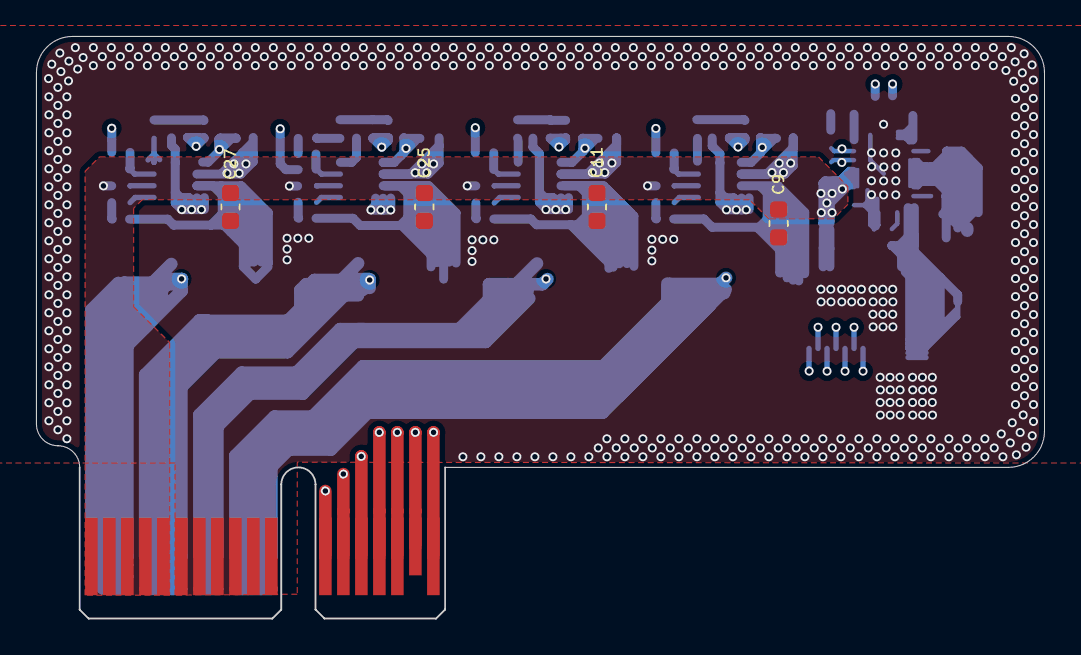
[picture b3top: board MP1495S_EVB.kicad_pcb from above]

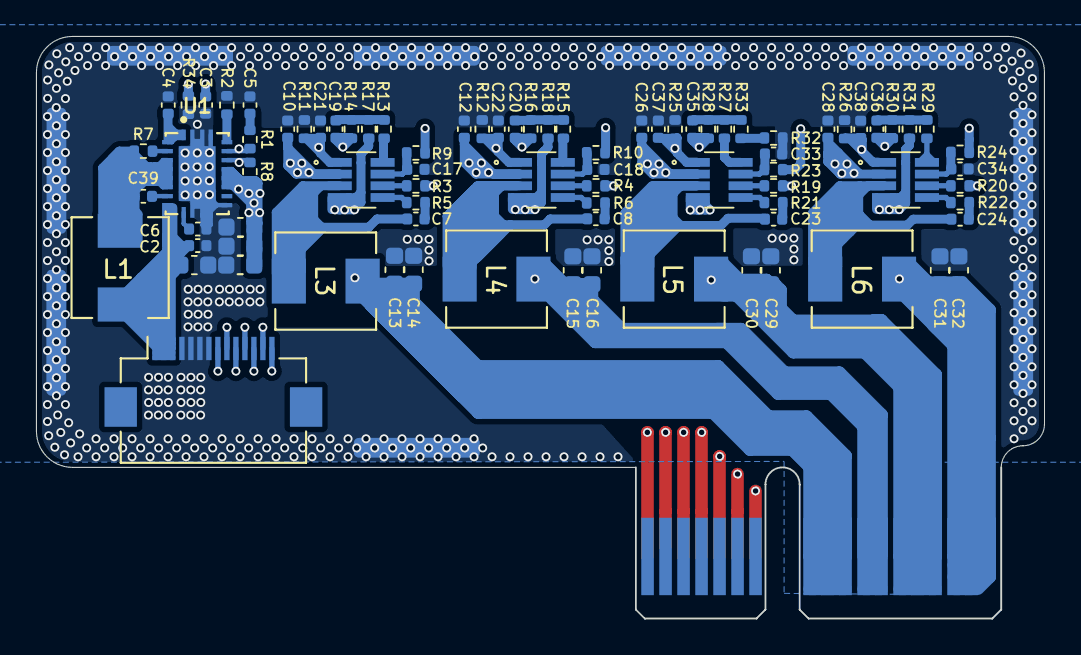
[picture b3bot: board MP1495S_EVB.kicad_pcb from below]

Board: 4 copper layers, 56.0 x 32.3 mm, 97 parts (92 on the bottom side), 56 nets.

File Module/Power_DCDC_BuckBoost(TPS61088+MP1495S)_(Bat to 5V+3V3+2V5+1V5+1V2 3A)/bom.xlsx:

标号 | 数量/板 | 值 | 备注 | 封装 | 数量 | 单价 | 总价
C1, C9, C11, C25, C27 | 5 | 10uF |  | 0603 | 100 | 0 | 0
C2, C7, C8, C10, C12, C17, C18, C23, C24, C26, C28, C33, C34, C39 | 14 | 0.1uF |  | 0402 | 100 | 0 | 0
C3 | 1 | 47pF |  | 0402 | 100 | 0 | 0
C4 | 1 | 1uF |  | 0402 | 100 | 0 | 0
C5, C21, C22, C37, C38 | 5 | 1nF |  | 0402 | 100 | 0 | 0
C6 | 1 | 8.2nF |  | 0402 | 100 | 0 | 0
C13, C14, C15, C16, C29, C30, C31, C32, C40, C41, C42 | 11 | 22uF |  | 0603 | 100 | 0 | 0
C19, C20, C35, C36 | 4 | 15pF |  | 0402 | 100 | 0 | 0
L1 | 1 | 1uH |  | 0530 | 100 | 0 | 0
L3 | 1 | 4.7uH |  | 0530 | 100 | 0 | 0
L4 | 1 | 3.3uH |  | 0530 | 100 | 0 | 0
L5 | 1 | 2.2uH |  | 0530 | 100 | 0 | 0
L6 | 1 | 1.5uH |  | 0530 | 100 | 0 | 0
R1 | 1 | 23.7K |  | 0402 | 100 | 0 | 0
R2 | 1 | 113K |  | 0402 | 100 | 0 | 0
R3, R4, R9, R10, R19, R20, R23, R24 | 8 | 100K (1%) |  | 0402 | 100 | 0 | 0
R5, R6, R21, R22 | 4 | 10(1%) |  | 0402 | 100 | 0 | 0
R7 | 1 | 267K |  | 0402 | 100 | 0 | 0
R8 | 1 | 220K |  | 0402 | 100 | 0 | 0
R11 | 1 | 11.3K(1%) |  | 0402 | 100 | 0 | 0
R12 | 1 | 10K(1%) |  | 0402 | 100 | 0 | 0
R13, R15 | 2 | 33K(1%) |  | 0402 | 100 | 0 | 0
R14, R16 | 2 | 40.2K (1%) |  | 0402 | 100 | 0 | 0
R17 | 1 | 13K (1%) |  | 0402 | 100 | 0 | 0
R18 | 1 | 19.1K (1%) |  | 0402 | 100 | 0 | 0
R25, R26 | 2 | 9.31K (1%) |  | 0402 | 100 | 0 | 0
R27 | 1 | 56K (1%) |  | 0402 | 100 | 0 | 0
R28, R30 | 2 | 30.1K (1%) |  | 0402 | 100 | 0 | 0
R29 | 1 | 82K (1%) |  | 0402 | 100 | 0 | 0
R31 | 1 | 61.9K (1%) |  | 0402 | 100 | 0 | 0
R32 | 1 | 20K (1%) |  | 0402 | 100 | 0 | 0
R33 | 1 | 15K (1%) |  | 0402 | 100 | 0 | 0
R34 | 1 | 69.8K |  | 0402 | 100 | 0 | 0
J1 | 1 | Conn_01x14 |  | FPC:14S-0.5SH | 20 | 0 | 0
U1 | 1 | TPS61088RHLR |  | TPS61088RHLR | 20 | 0 | 0
1V2, 1V5, 2V5, 3V3 | 4 | MP1495S |  | SOT65P280X100-8N | 20 | 0 | 0
